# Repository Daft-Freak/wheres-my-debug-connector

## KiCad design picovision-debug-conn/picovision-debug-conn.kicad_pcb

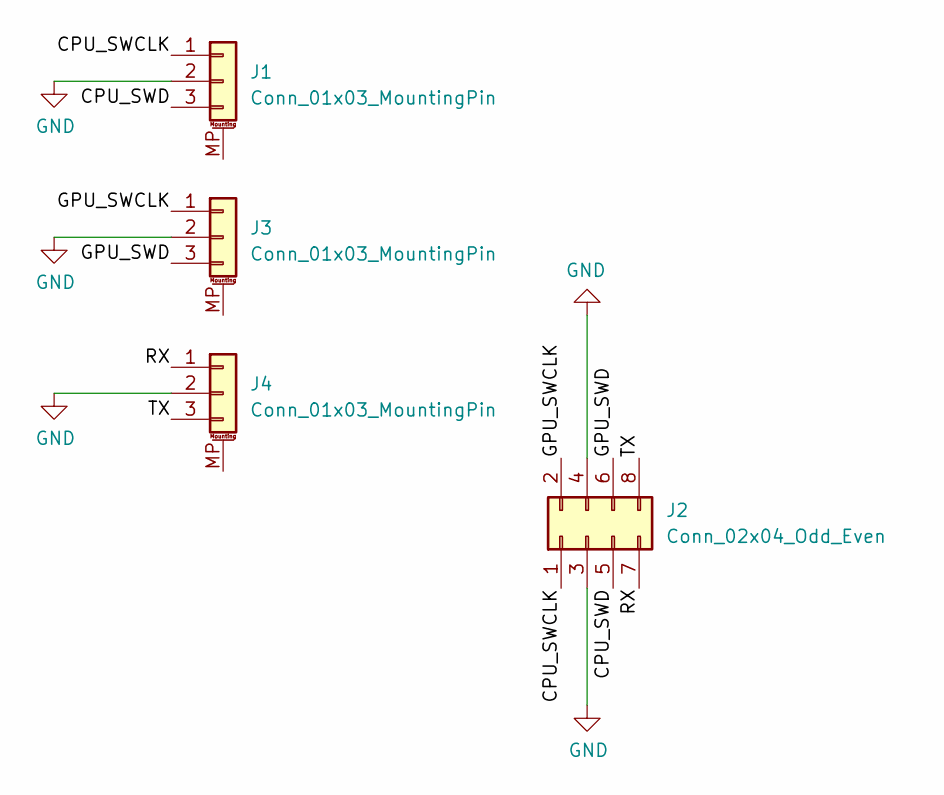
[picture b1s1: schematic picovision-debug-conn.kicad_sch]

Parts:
J1, J3, J4: Conn_01x03_MountingPin; JST_SH_SM03B-SRSS-TB_1x03-1MP_P1.00mm_Horizontal
J2: Conn_02x04_Odd_Even; PinHeader_2x04_P2.54mm_Vertical

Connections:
/CPU_SWCLK: J1.1, J2.1
/CPU_SWD: J1.3, J2.5
/GPU_SWCLK: J2.2, J3.1
/GPU_SWD: J2.6, J3.3
/RX: J2.7, J4.1
/TX: J2.8, J4.3
GND: J1.2, J2.3, J2.4, J3.2, J4.2

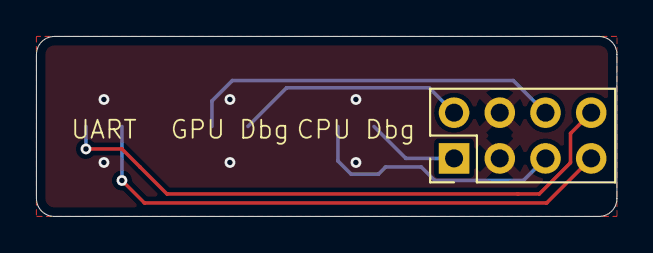
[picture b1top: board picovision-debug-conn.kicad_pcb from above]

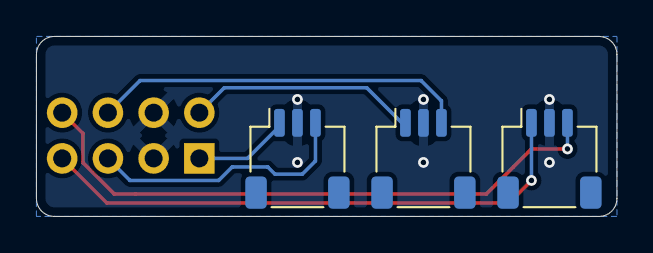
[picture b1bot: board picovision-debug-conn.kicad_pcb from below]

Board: 2 copper layers, 32.2 x 10.0 mm, 4 parts (3 on the bottom side), 7 nets.

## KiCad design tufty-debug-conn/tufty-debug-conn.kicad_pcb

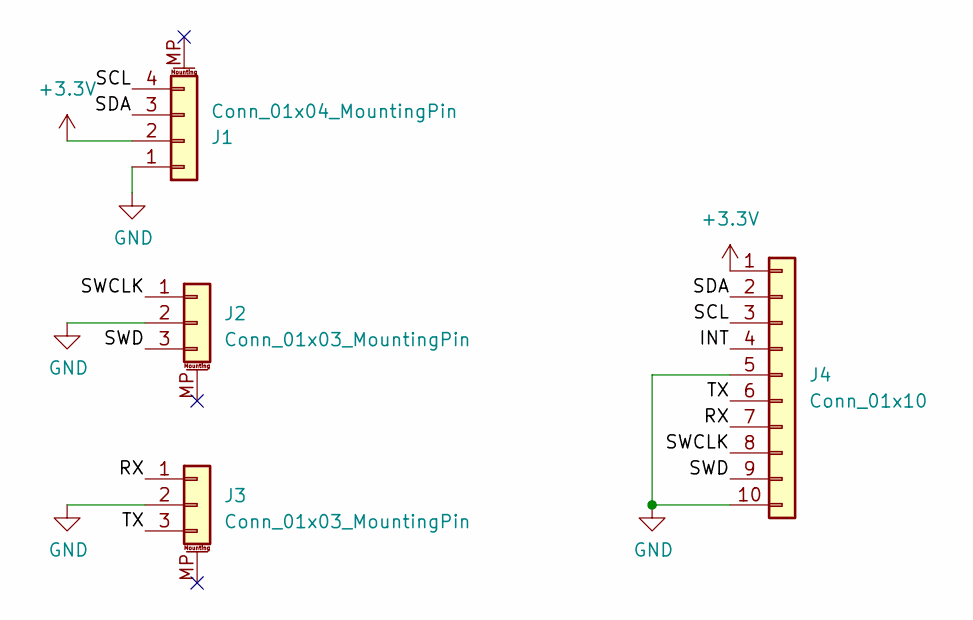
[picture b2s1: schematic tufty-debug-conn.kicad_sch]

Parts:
J1: Conn_01x04_MountingPin; JST_SH_SM04B-SRSS-TB_1x04-1MP_P1.00mm_Horizontal
J2, J3: Conn_01x03_MountingPin; JST_SH_SM03B-SRSS-TB_1x03-1MP_P1.00mm_Horizontal
J4: Conn_01x10; PinHeader_1x10_P2.54mm_Vertical

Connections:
+3.3V: J1.2, J4.1
/INT: J4.4
/RX: J3.1, J4.7
/SCL: J1.4, J4.3
/SDA: J1.3, J4.2
/SWCLK: J2.1, J4.8
/SWD: J2.3, J4.9
/TX: J3.3, J4.6
GND: J1.1, J2.2, J3.2, J4.5, J4.10

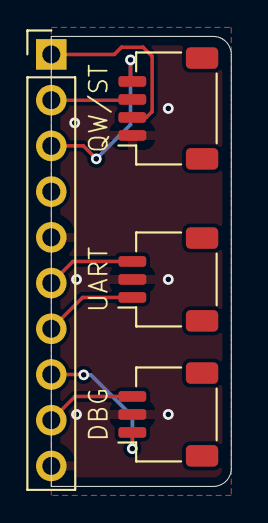
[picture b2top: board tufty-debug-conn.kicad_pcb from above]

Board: 2 copper layers, 10.0 x 25.0 mm, 4 parts (0 on the bottom side), 8 nets.

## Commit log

2024-12-24 Tufty
2024-12-24 PicoVision
